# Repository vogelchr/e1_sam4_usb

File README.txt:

** Review comments for version

commit af33165416c78bff5535539db3183336a3adedb6
    Changed LIU to IDT82V2081.

OPEN:

* Board Bringup
	- due to PLL restrictions we cannot generate PCK 2.048 MHz, have
	  to live with SSC clk output (-> remove sam4s Pin 6,
	     PB3 to TX_CLK, PA21 to CLK2048)
	  
	- LIU spi interface configuration, pull SCLKE up (now: gnd)
	    SCLKE=low: shift SDO on rising edge of SCLK  (datasheet page 13)
	    SCLKE=high: shift SDO on falling edge of SCLK
	  SDI is *always* sampled on the rising edge, so to be consistent
	  SDI will be shifted on the falling edge, so should SDO and SCLKE
	  should be HIGH

	- rename LEDs to match net numbers (LED1..LED3)

* New Features

	For generating the E1 frame sync signal to the SSC peripheral:
	- bridge PA20/Pin16/RF (Receive Frame) to
	         PA27/Pin37/TIOB2 (Timer 2, IO B)
	         
	- bridge PA29/Pin41/TCLK2 (ext. clock input 2 to timer) to
	         PA19/Pin13/RK (Receive Clock)

* Repository / File Formats
	- rename .brd/.sch to sensible name, integrate in old
	   http://cgit.osmocom.org/osmo-e1-xcvr/ repository.

DONE after 20180624:
	- EAGLE 7 compatibility
		(exported _v7 files)
	- make JTAGSEL pullup DNP (JTAGSEL, TEST, ERASE should float)
	- ERASE jumper
	- pullups on i2c
	- pullups on SPI \CSn

	- possibly switch to 82V2081 LUI, as a few people have successfully
	  experimented with it, has access to nice stats over SPI
	  https://www.idt.com/products/interface-connectivity/telecom-interface-products/t1j1e1-interface-products/82v2081-1-channel-t1-j1-e1-short-haullong-haul-liu

DONE after 20180625:
	 - USB has no transient voltage suppressor, possible ESD damage
	 (recommended: IP4234CZ6)
	- R1 120 Ohms (LIU Rx term)
	- R2, R8 9 Ohms (LIU Tx in series)
	- LIU move signal from LOS to #INT 
	  -> Interrupt can be generated on LOS anyway.
	 - diescrete resistors instead of U$2 resistor array is probably lower
	cost in SMT, as it's a standard 10k resistor reel and not one more
	"cut-tape" reel only for that part
		-> introduced quad resistor packs 10k for various pullups
	 - for the DAC, it might make sense to align with what sylvain is using
	in his FPGA based design (and what sysmocom has used in other designs):
	MAX5215 (14bit). Could be upgraded to 16bit MAX5217 if ever needed.
	 - UART has not transient voltage suppressor, possible ESD damage
	(recommended: IP4234CZ6)
	 - JTAG connector doesn't appear to have standard 2x10 ARM-JTAG pin-out.
	If there's space I'd prefer a 20pin ARM-JTAG.
	 - SV3 serial pin-out could be aligned with FTDI 1x5 (or 1x6?) usb
	serial cables. I think it makes sense to align with pin-out of industry
	standard cables that people might already have
	- LEDs near frontpanel
	 - does SPI+I2C header (SV6) have UEXT compatible pin-out? If we use a
	 2x5 header, it might make senese to use the olimex-standard UEXT format
	 as there are plenty of other boards/devices with that pin-out
	 - !RESET has no pull-up, design is possibly susceptible to picking up
	RF/noise as reset trigger
	 - UART has no pull-up resistor on RxD input, i.e. floating input unless
	UART is connected
	- add pullup on LIU #RST
	 - GPS antenna input has no transient voltage suppressor, possible ESD
	damage (unless the
	GNS module has one inside? Did you find any documentation on that in
	the module data sheet? Recommended: 0603ESDA-TR

	 - GPS receiver rx/tx/pps doen't have series termination (27R or
	the like), possibly resulting in switching tranients degrading GPS
	performance

	(this was refused earlier, but later on implemented:)
	 - might make sense to add a precision voltage reference for the DAC,
	e.g. MAX6163ESA?

	- 33R series resistance in oscillator outputs

	- edge type SMA replaced by through hole (edge type incompatible
	  with frontpanel directly on board edge, would have meant to do
	  milling)

REFUSED:
	- interface to old LIU only board (SPI + DATA on pinheader)

	 - 1k series resistors for LEDs seems quite high resistance for 3.3V. I
	would usually expect 330..680 Ohms there?
	  => with modern LEDs it's really bright enough, even with 1k (or even 5k)

	 - If inverted-logic signals would use !SIGNAL instead of #SIGNAL, EAGLE
	would over-stroke their names
	  => (vogelchr) Nice, didn't know this, but will probably not change.

	- USB_VBUS_SENS not routed to microcontroller!
	  device is bus powered, hence monitoring not needed!

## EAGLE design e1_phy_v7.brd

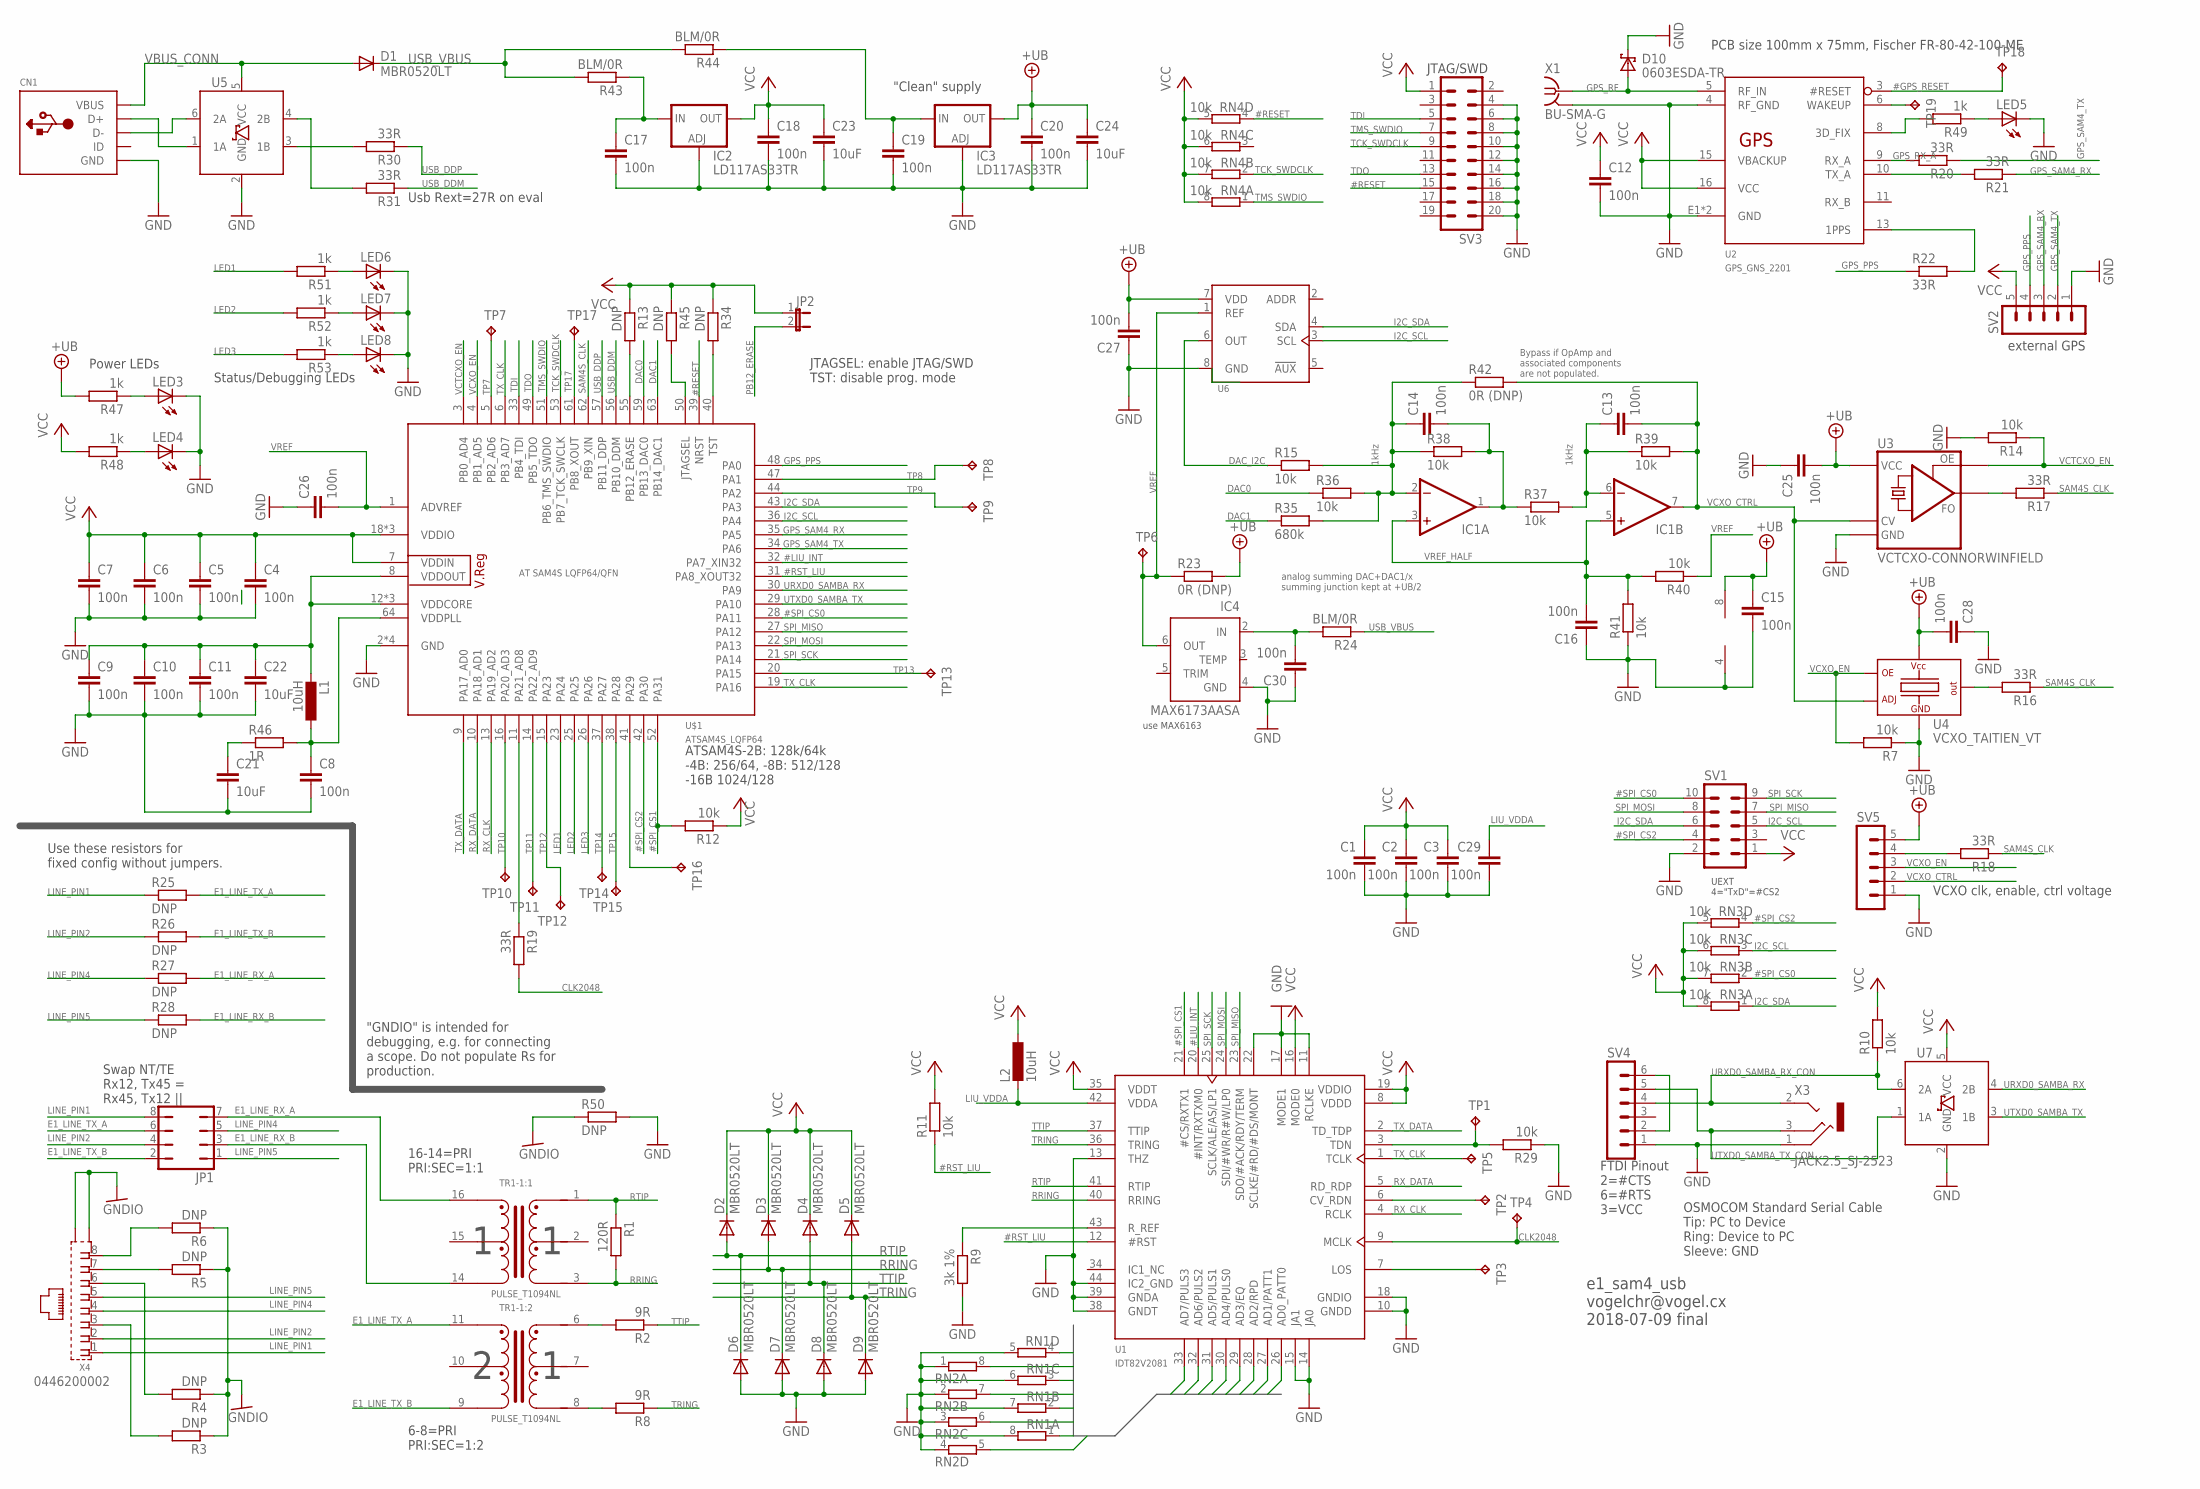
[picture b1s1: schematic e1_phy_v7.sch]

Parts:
C1, C2, C3, C4, C5, C6, C7, C8, C9, C10, C11, C12, C13, C14, C15, C16, C17, C18, C19, C20, C25, C26, C27, C28, C29, C30: 100n; C0603
C21, C22, C23, C24: 10uF; C0603
CN1: USBMINIB; USB-MINIB
D1, D2, D3, D4, D5, D6, D7, D8, D9: MBR0520LT; SOD123
D10: 0603ESDA-TR; 0603
IC1: 2AMP_P8+4D; SO08
IC2, IC3: LD117AS33TR; SOT223
IC4: MAX6173AASA; SO08
JP1: JP4Q
JP2: JP1E; JP1
L1, L2: 10uH; L1812
LED3, LED4, LED5, LED6, LED7, LED8: LEDCHIPLED_0603; CHIPLED_0603
R1: 120R; R0603
R2, R8: 9R; R0603
R3, R4, R5, R6, R13, R25, R26, R27, R28, R34, R45, R50: DNP; R0603
R7, R10, R11, R12, R14, R15, R29, R36, R37, R38, R39, R40, R41: 10k; R0603
R9: 3k 1%; R0603
R16, R17, R18, R19, R20, R21, R22, R30, R31: 33R; R0603
R23, R42: 0R (DNP); R0603
R24, R43, R44: BLM/0R; R0603
R35: 680k; R0603
R46: 1R; R0603
R47, R48, R49, R51, R52, R53: 1k; R0603
RN1, RN2: 4R-NEXB38V; EXB38V
RN3, RN4: 10k; EXB38V
SV1: MA05-2
SV2, SV5: MA05-1
SV3: MA10-2
SV4: MA06-1
TP1, TP2, TP3, TP4, TP5, TP6, TP7, TP8, TP9, TP10, TP11, TP12, TP13, TP14, TP15, TP16, TP17, TP18, TP19: TPB1,27; B1,27
TR1: PULSE_T1094NL; PULSE_BH
U1: IDT82V2081; TQFP44
U2: GPS_GNS_2201
U3: VCTCXO-CONNORWINFIELD
U4: VCXO_TAITIEN_VT; VCXO_TAITIEN_VT_7MM_5MM
U5, U7: IP4234CZ6; TSOP-6
U6: MAX521X; UMAX8
U$1: ATSAM4S_LQFP64; LQFP-ST-64-2
X1: BU-SMA-G
X3: JACK2.5_SJ-2523
X4: 0446200002

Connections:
#GPS_RESET: TP18.TP, U2.3 (#RESET)
#LIU_INT: U1.20 (#INT/RXTXM0), U$1.32 (PA7_XIN32)
#RESET: RN4.4 (1), SV3.15, U$1.39 (NRST)
#RST_LIU: R11.1, U1.12 (#RST), U$1.31 (PA8_XOUT32)
#SPI_CS0: RN3.2 (1), SV1.10, U$1.28 (PA11)
#SPI_CS1: R12.2, U1.21 (#CS/RXTX1), U$1.52 (PA31)
#SPI_CS2: RN3.4 (1), SV1.4, U$1.42 (PA30)
+UB: C15.1, C20.1, C24.1, C25.2, C27.2, C28.2, IC1.8 (V+), IC3.4 (OUT), R23.2, R47.2, SV5.5, U3.9 (VCC), U4.6 (VCC), U6.7 (VDD)
AD0: RN2.8 (2), U1.26 (AD0_PATT0)
AD1: RN2.7 (2), U1.27 (AD1/PATT1)
AD2: RN2.6 (2), U1.28 (AD2/RPD)
AD3: RN2.5 (2), U1.29 (AD3/EQ)
AD4: RN1.4 (1), U1.30 (AD4/PULS0)
AD5: RN1.3 (1), U1.31 (AD5/PULS1)
AD6: RN1.2 (1), U1.32 (AD6/PULS2)
AD7: RN1.1, U1.33 (AD7/PULS3)
CLK2048: R19.2, TP4.TP, U1.9 (MCLK)
CLK2048_SAM4S: R19.1, U$1.11 (PA21_AD8)
DAC0: R36.1, U$1.59 (PB13_DAC0)
DAC1: R35.1, U$1.63 (PB14_DAC1)
DAC_I2C: R15.1, U6.6 (OUT)
E1_LINE_RX_A: JP1.7, R27.2, TR1.16
E1_LINE_RX_B: JP1.3, R28.2, TR1.14
E1_LINE_TX_A: JP1.6, R25.2, TR1.11
E1_LINE_TX_B: JP1.2, R26.2, TR1.9
GND: C1.2, C2.2, C3.2, C4.2, C5.2, C6.2, C7.2, C8.2, C9.2, C10.2, C11.2, C12.2, C15.2, C16.1, C17.2, C18.2, C19.2, C20.2, C21.2, C22.2, C23.2, C24.2, C25.1, C26.1, C27.1, C28.1, C29.2, C30.1, CN1.GND, D6.A, D7.A, D8.A, D9.A, D10.2 (K), IC1.4 (V-), IC2.1 (ADJ), IC3.1 (ADJ), IC4.4 (GND), LED3.C, LED4.C, LED5.C, LED6.C, LED7.C, LED8.C, R7.1, R9.2, R14.2, R29.1, R41.1, R50.2, RN1.5 (2), RN1.6 (2), RN1.7 (2), RN1.8 (2), RN2.1, RN2.2 (1), RN2.3 (1), RN2.4 (1), SV1.2, SV2.1, SV3.4, SV3.6, SV3.8, SV3.10, SV3.12, SV3.14, SV3.16, SV3.18, SV3.20, SV4.1, SV5.1, U1.10 (GNDD), U1.11 (RCLKE), U1.13 (THZ), U1.14 (JA0), U1.15 (JA1), U1.17 (MODE1), U1.18 (GNDIO), U1.22 (SCLKE/#RD/#DS/MONT), U1.38 (GNDT), U1.39 (GNDA), U1.44 (IC2_GND), U2.4 (RF_GND), U2.E1 (GND), U2.E2 (GND), U3.4 (GND), U4.3 (GND), U5.2 (GND), U6.8 (GND), U7.2 (GND), U$1.2 (GND), U$1.17 (GND), U$1.46 (GND), U$1.60 (GND), X1.2, X1.3 (2), X1.4 (2), X1.5 (2), X3.1 (RING)
GNDIO: R3.1, R4.1, R5.1, R6.1, R50.1, X4.S@1 (S1), X4.S@2 (S2)
GPS_3DFIX: R49.2, U2.8 (3D_FIX)
GPS_PPS: R22.1, SV2.4, U$1.48 (PA0)
GPS_RF: D10.1 (A), U2.5 (RF_IN), X1.1
GPS_RX_A: R20.2, U2.9 (RX_A)
GPS_SAM4_RX: R21.1, SV2.3, U$1.35 (PA5)
GPS_SAM4_TX: R20.1, SV2.2, U$1.34 (PA6)
GPS_WAKEUP: TP19.TP, U2.6 (WAKEUP)
I2C_SCL: RN3.3 (1), SV1.5, U6.3 (SCL), U$1.36 (PA4)
I2C_SDA: RN3.1, SV1.6, U6.4 (SDA), U$1.43 (PA3)
JTAGSEL: R45.2, U$1.50 (JTAGSEL)
LED1: R51.2, U$1.23 (PA24)
LED2: R52.2, U$1.25 (PA25)
LED3: R53.2, U$1.26 (PA26)
LINE_PIN1: JP1.8, R25.1, X4.1
LINE_PIN2: JP1.4, R26.1, X4.2
LINE_PIN3: R3.2, X4.3
LINE_PIN4: JP1.5, R27.1, X4.4
LINE_PIN5: JP1.1, R28.1, X4.5
LINE_PIN6: R4.2, X4.6
LINE_PIN7: R5.2, X4.7
LINE_PIN8: R6.2, X4.8
LIU_VDDA: C29.1, L2.2, U1.42 (VDDA)
unnamed: CN1.D+, U5.1 (1A)
unnamed: CN1.D-, U5.6 (2A)
unnamed: TP2.TP, U1.6 (CV_RDN)
unnamed: R2.2, TR1.6
unnamed: R29.2, TP1.TP, U1.3 (TDN)
unnamed: TP3.TP, U1.7 (LOS)
unnamed: C30.2, IC4.2 (IN), R24.2
unnamed: LED5.A, R49.1
unnamed: C19.1, IC3.3 (IN), R44.1
unnamed: C17.1, IC2.3 (IN), R43.1
unnamed: C21.1, R46.1
unnamed: LED3.A, R47.1
unnamed: TP16.TP, U$1.41 (PA29)
unnamed: LED4.A, R48.1
unnamed: R8.2, TR1.8
unnamed: LED6.A, R51.1
unnamed: LED7.A, R52.1
unnamed: LED8.A, R53.1
unnamed: R22.2, U2.13 (1PPS)
unnamed: R9.1, U1.43 (R_REF)
unnamed: SV4.2, SV4.6
OPAMP1_IN_NEG: C14.1, IC1.2 (-IN), R15.2, R35.2, R36.2, R38.1, R42.1
OPAMP1_OUT: C14.2, IC1.1 (OUT), R37.1, R38.2
OPAMP2_IN_NEG: C13.1, IC1.6 (-IN), R37.2, R39.1
PB12_ERASE: JP2.2, R13.2, U$1.55 (PB12_ERASE)
RRING: D3.A, D7.C, R1.2, TR1.3, U1.40 (RRING)
RTIP: D2.A, D6.C, R1.1, TR1.1, U1.41 (RTIP)
RX_CLK: U1.4 (RCLK), U$1.13 (PA19_AD2)
RX_DATA: U1.5 (RD_RDP), U$1.10 (PA18_AD1)
SAM4S_CLK: R16.1, R17.1, R18.1, U$1.62 (PB9_XIN)
SAM4S_CLK_EXT: R18.2, SV5.4
SAM4S_CLK_VCTXO: R17.2, U3.5 (FO)
SAM4S_CLK_VCXO: R16.2, U4.4 (Q)
SPI_MISO: SV1.7, U1.23 (SDO/#ACK/RDY/TERM), U$1.27 (PA12)
SPI_MOSI: SV1.8, U1.24 (SDI/#WR/R#W/LP0), U$1.22 (PA13)
SPI_SCK: SV1.9, U1.25 (SCLK/ALE/AS/LP1), U$1.21 (PA14)
TCK_SWDCLK: RN4.2 (1), SV3.9, U$1.53 (PB7_TCK_SWCLK)
TDI: SV3.5, U$1.33 (PB4_TDI)
TDO: SV3.13, U$1.49 (PB5_TDO)
TMS_SWDIO: RN4.1, SV3.7, U$1.51 (PB6_TMS_SWDIO)
TP7: TP7.TP, U$1.5 (PB2_AD6)
TP8: TP8.TP, U$1.47 (PA1)
TP9: TP9.TP, U$1.44 (PA2)
TP10: TP10.TP, U$1.16 (PA20_AD3)
TP11: TP11.TP, U$1.14 (PA22_AD9)
TP12: TP12.TP, U$1.15 (PA23)
TP13: TP13.TP, U$1.20 (PA15)
TP14: TP14.TP, U$1.37 (PA27)
TP15: TP15.TP, U$1.38 (PA28)
TP17: TP17.TP, U$1.61 (PB8_XOUT)
TPS_TX_A: R21.2, U2.10 (TX_A)
TRING: D5.A, D9.C, R8.1, U1.36 (TRING)
TST: R34.2, U$1.40 (TST)
TTIP: D4.A, D8.C, R2.1, U1.37 (TTIP)
TX_CLK: TP5.TP, U1.1 (TCLK), U$1.6 (PB3_AD7), U$1.19 (PA16)
TX_DATA: U1.2 (TD_TDP), U$1.9 (PA17_AD0)
URXD0_SAMBA_RX: U7.4 (2B), U$1.30 (PA9)
URXD0_SAMBA_RX_CON: R10.1, SV4.4, U7.6 (2A), X3.2 (TIP)
USB_DDM: R31.1, U$1.56 (PB10_DDM)
USB_DDM_CON: R31.2, U5.4 (2B)
USB_DDP: R30.1, U$1.57 (PB11_DDP)
USB_DDP_CON: R30.2, U5.3 (1B)
USB_VBUS: D1.C, R24.1, R43.2, R44.2
UTXD0_SAMBA_TX: U7.3 (1B), U$1.29 (PA10)
UTXD0_SAMBA_TX_CON: SV4.5, U7.1 (1A), X3.3 (MIDDLE)
VBUS_CONN: CN1.VBUS, D1.A, U5.5 (VCC)
VCC: C1.1, C2.1, C3.1, C4.1, C5.1, C6.1, C7.1, C12.1, C18.1, C23.1, D2.C, D3.C, D4.C, D5.C, IC2.4 (OUT), JP2.1, L2.1, R10.2, R11.2, R12.1, R13.1, R34.1, R45.1, R48.2, RN3.5 (2), RN3.6 (2), RN3.7 (2), RN3.8 (2), RN4.5 (2), RN4.6 (2), RN4.7 (2), RN4.8 (2), SV1.1, SV2.5, SV3.1, U1.8 (VDDD), U1.16 (MODE0), U1.19 (VDDIO), U1.35 (VDDT), U2.15 (VBACKUP), U2.16 (VCC), U7.5 (VCC), U$1.7 (VDDIN), U$1.18 (VDDIO), U$1.45 (VDDIO), U$1.58 (VDDIO)
VCTCXO_EN: R14.1, U3.8 (OE), U$1.3 (PB0_AD4)
VCXO_CTRL: C13.2, IC1.7 (OUT), R39.2, R42.2, SV5.2, U3.10 (CV), U4.1 (VADJ)
VCXO_EN: R7.2, SV5.3, U4.2 (OE), U$1.4 (PB1_AD5)
VDDCORE: C9.1, C10.1, C11.1, C22.1, L1.2, U$1.8 (VDDOUT), U$1.12 (VDDCORE), U$1.24 (VDDCORE), U$1.54 (VDDCORE)
VDDPLL: C8.1, L1.1, R46.2, U$1.64 (VDDPLL)
VREF: C26.2, IC4.6 (OUT), R23.1, R40.1, TP6.TP, U6.1 (REF), U$1.1 (ADVREF)
VREF_HALF: C16.2, IC1.3 (+IN), IC1.5 (+IN), R40.2, R41.2

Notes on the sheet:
Swap NT/TE Rx12, Tx45 = Rx45, Tx12 ||
Use these resistors for fixed config without jumpers.
"GNDIO" is intended for debugging, e.g. for connecting a scope. Do not populate Rs for production.
Bypass if OpAmp and associated components are not populated.
1kHz
analog summing DAC+DAC1/x summing junction kept at +UB/2
"Clean" supply
JTAGSEL: enable JTAG/SWD TST: disable prog. mode
JTAG/SWD
external GPS
OSMOCOM Standard Serial Cable Tip: PC to Device Ring: Device to PC Sleeve: GND
ATSAM4S-2B: 128k/64k -4B: 256/64, -8B: 512/128 -16B 1024/128
Usb Rext=27R on eval
PCB size 100mm x 75mm, Fischer FR-80-42-100-ME
Status/Debugging LEDs
VCXO clk, enable, ctrl voltage
16-14=PRI PRI:SEC=1:1
6-8=PRI PRI:SEC=1:2
e1_sam4_usb vogelchr@vogel.cx 2018-07-09 final
FTDI Pinout 2=#CTS 6=#RTS 3=VCC
UEXT 4="TxD"=#CS2
Power LEDs
use MAX6163

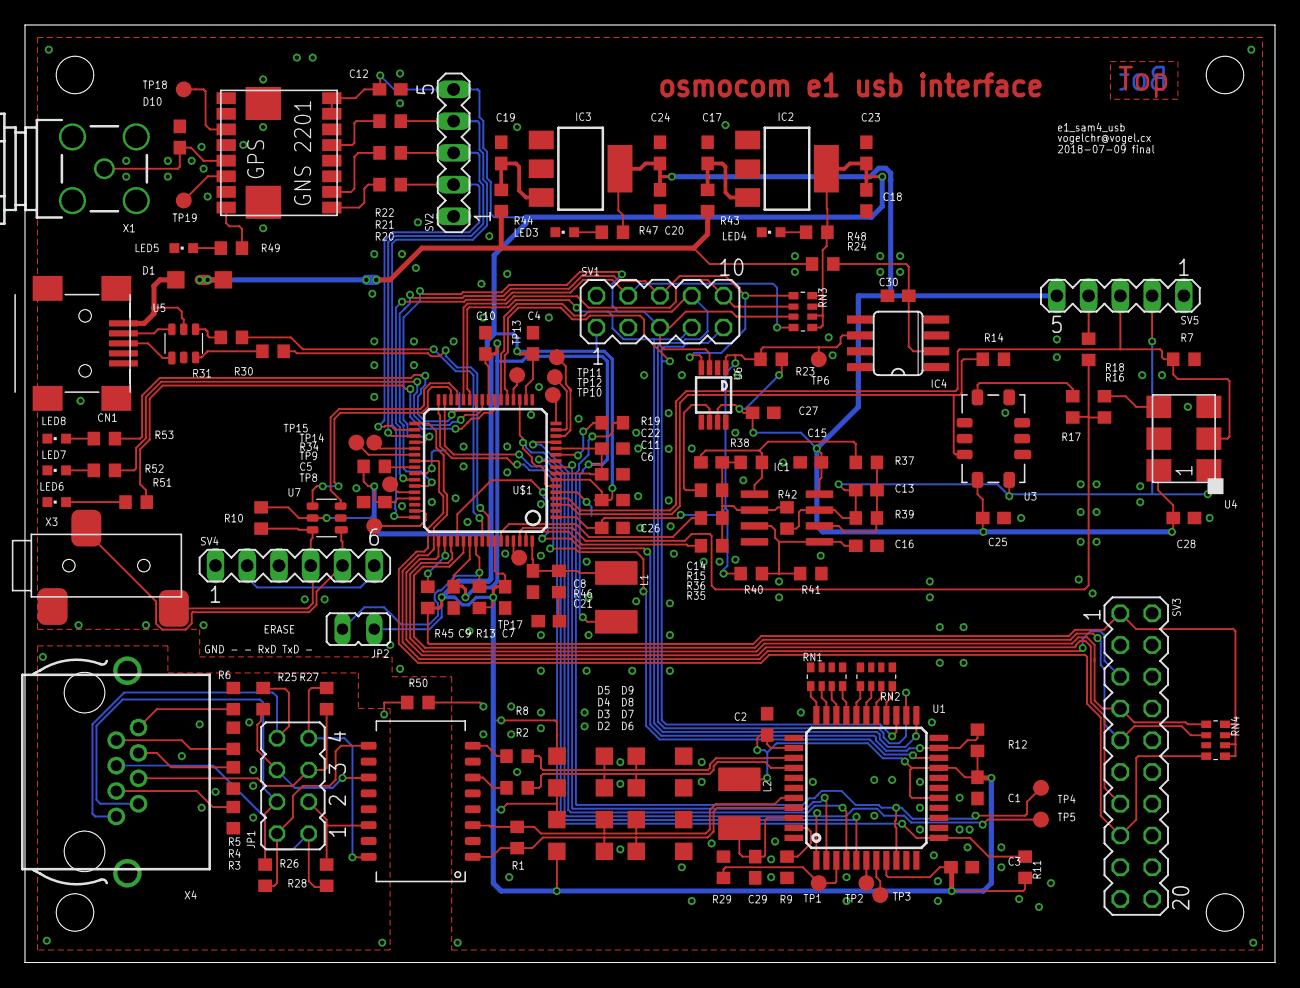
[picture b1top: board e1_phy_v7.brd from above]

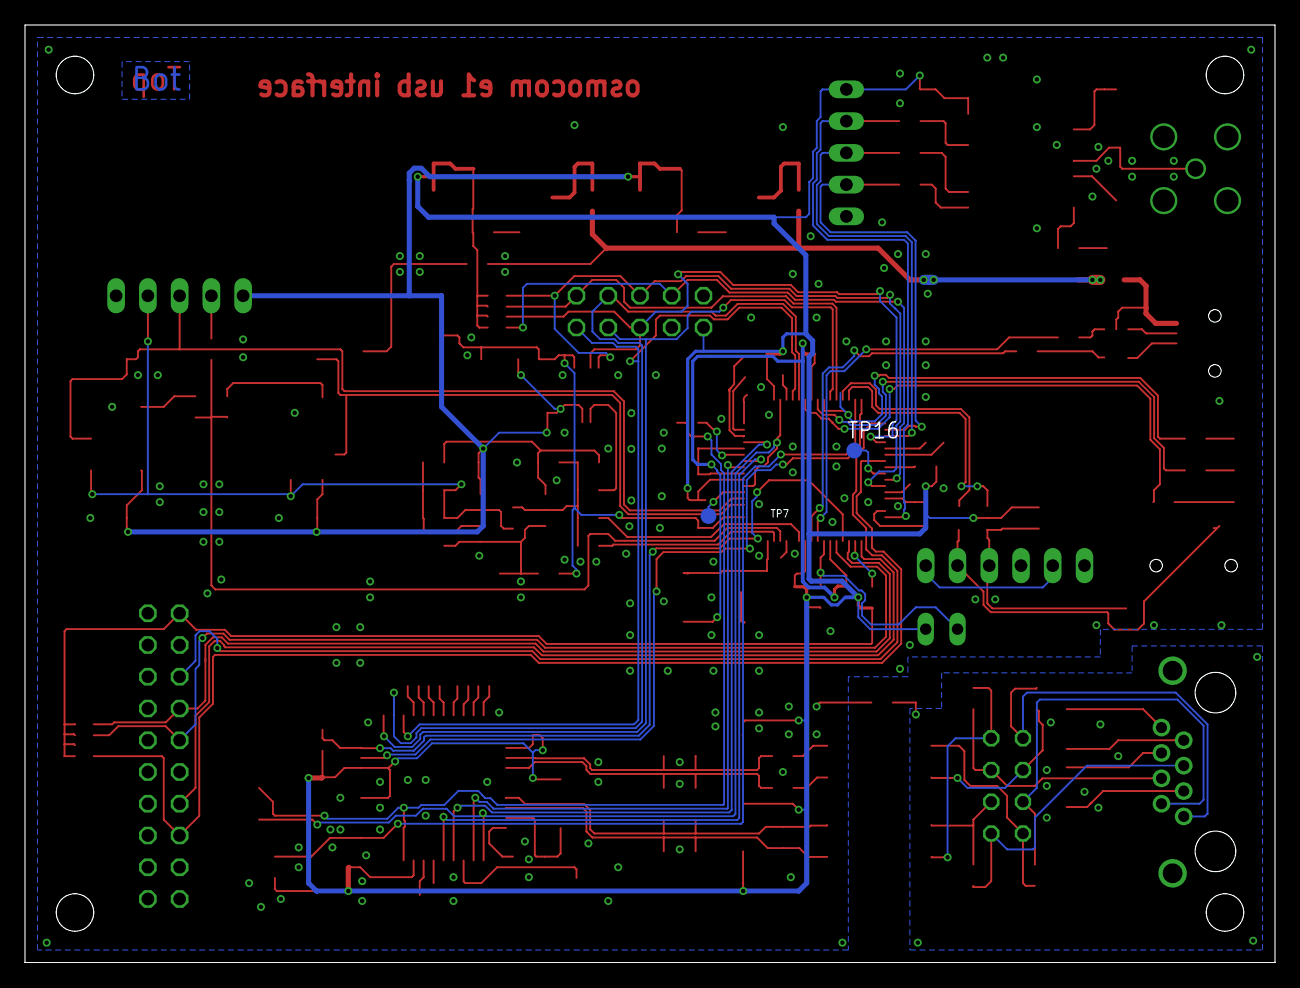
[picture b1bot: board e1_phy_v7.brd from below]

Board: 2 copper layers, 100.0 x 75.0 mm, 146 parts (2 on the bottom side), 123 nets.

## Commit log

2018-05-16 First commit.
2018-06-24 First sane version, for review.
    I've smashed all the random edits and redesigns into this single commit,
    the history was not useful to keep.
2018-06-24 Add CAM output and .pdf version of schematic & board.
2018-06-25 collecting review comments
2018-06-25 review remarks
2018-06-25 Pullup on i2c, ERASE jumper.
2018-06-25 Changed LIU to IDT82V2081.
2018-06-25 Version for review, done on 20180625
2018-06-25 Library for IDT82v2081 LIU.
2018-06-25 Add worksheet with pin allocation for SAM4S.
2018-06-27 Reviev comments.
2018-06-27 Readme added review comments from LaF0rge (thanks!).
2018-06-27 My notes on LaF0rges comments.
2018-06-27 Add laforge.lbr.
    https://osmocom.org/attachments/3247/laforge.lbr
2018-06-27 Implement review: ESD protection on USB.
2018-06-27 Implement review comment: R1 120 Ohms, R2, R2 9 Ohs
    Termination on Rx input and output impedance on Tx.
2018-06-27 Implement review comment: LIU move signal from LOS to #INT
    - LIU move signal from LOS to #INT
    -> Interrupt can be generated on LOS anyway.
2018-06-27 Implementation of review comment:
    Removed octal resistor array, introduced quad resistor array,
    will be used for various pullups.
2018-06-27 Implement review comments: Switch DAC to Maxim part.
2018-06-27 More review comments implemented.
    Done:
    - ESD protection on UART
    - changed JTAG to 2x10 standard ARM (but only minimal usage of pins on
    SAM4S)
    - FTDI pinout on serial port header
    - LEDS moved near frontpanel, maybe later exchange by side-emitting
2018-07-03 Implementing further review comments:
    * SPI/I2C header UEXT compatible 2x5
    * Pullups on #RESET & JTAG TCK, TMS = SWDIO, SWCK
    * Pullup on UART RX
    * Pullup on Liu #RST
2018-07-03 Moved LIU VDD_analog from +UB to Vcc+Inductor
    (this is suggested in the datasheet, and I don't want to
    pollute the +UB (clean supply for oscillators))
2018-07-03 Review comments: Add ESD protection on GPS antenna.
    0603ESDA-TR from laforge library.
2018-07-03 Regenerated v7 eagle files, made .pdf for schematic.
    -> next release candidate 20180703
2018-07-03 Library for MAX5215 / MAX5217 i2c DAC
2018-07-04 Review comments from LaF0rge.
2018-07-07 33R series resistor in clocks, RX/TX of PPS, SMA through hole
2018-07-07 (removed older comments from README I had only added to the github repo)
2018-07-07 Add footprint for voltage reference, can be bypassed.
2018-07-07 Testpads for unused LIU signals.
2018-07-07 Cleaned up silkscreen.
2018-07-09 cvogel.lbr: Fix typo in SAM4S/LQFP64 symbol.
2018-07-09 Some cleanup before declaring final.
    ADVREF of SAM4S fed by VREF net.
    +UB/2 divider fed by VREF net, renamed to VREF_HALF.
2018-10-13 Notes during board bringup.
